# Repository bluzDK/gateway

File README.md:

Bluz Gateway Hardware Files
==========
Bluz is a Development Kit (DK) that implements the Wiring language and talks to the [Particle](https://www.particle.io/) cloud through Bluetooth Low Energy. It can be accessed through a REST API and programmed from a Web IDE.

These files have been made available online through a [Creative Commons Attribution-ShareAlike 3.0](http://creativecommons.org/licenses/by-sa/3.0/) license.

You are welcome to distribute, remix, and use these files for commercial purposes. If you do so, please attribute the original design to Bluz both on the website and on the physical packaging of the product or in the instruction manual. All derivative works must be published under the same or a similar license.

All items are subject to change over time as the product is designed, so make sure you are always looking at the latest information by pulling often.

##Sections
<b>BOM</b>: Current Bill of Materials for the gateway.

<b>Datasheets</b>: Datasheets for all major parts on the board.

<b>HW Design</b>: Schematics, board layouts, and other design files.

<b>3D Files</b>: 3D Models of the PCBA and Case

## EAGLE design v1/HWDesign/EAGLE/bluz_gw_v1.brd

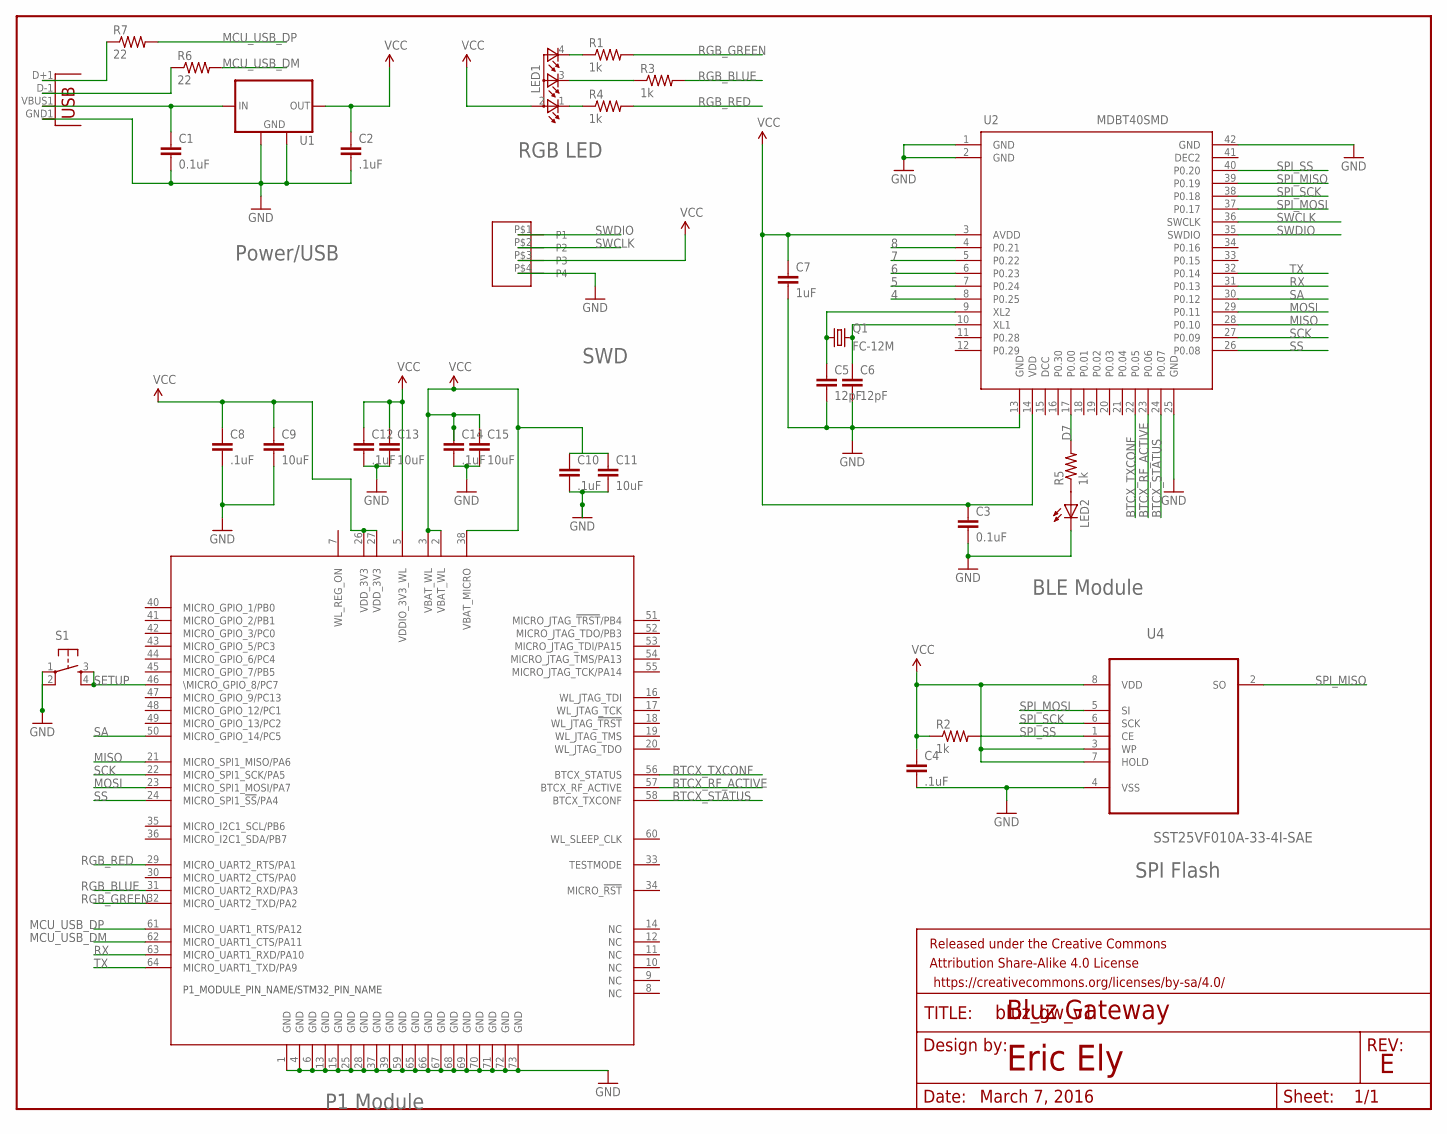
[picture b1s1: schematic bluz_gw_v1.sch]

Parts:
C1, C3: 0.1uF; 0603-CAP
C2, C4, C8, C10, C12, C14: .1uF; 0603-CAP
C5, C6: 12pF; 0603-CAP
C7: 1uF; 0603-CAP
C9, C11, C13, C15: 10uF; 0603-CAP
FRAME1: FRAME-LETTER; CREATIVE_COMMONS
JP2: USBA-SMD-MALE; USB-A-SMT-MALE
LED1: TOPLED-3PLCC; P-LCC-4-3
LED2: LEDCHIP-LED0603; CHIP-LED0603
Q1: FC-12M
R1, R2, R3, R4, R5: 1k; 0603-RES
R6, R7: 22; 0603-RES
S1: TAC_SWITCHSMD; TACTILE_SWITCH_SMD
U1: MCP1825S-SOT223; SOT223
U2: MDBT40SMD; MDBT40
U3: WM-N-BM-14
U4: SST25VF010A-33-4I-SAE; SOIC127P600X175-8N
U$3: POGO_CONNECTORPOGO_CONNECTOR; POGO_CONNECTER

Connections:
4: U2.8 (P0.25)
5: U2.7 (P0.24)
6: U2.6 (P0.23)
7: U2.5 (P0.22)
8: U2.4 (P0.21)
BTCX_RF_ACTIVE: U2.23 (P0.06), U3.57 (BTCX_RF_ACTIVE)
BTCX_STATUS: U2.24 (P0.07), U3.58 (BTCX_TXCONF)
BTCX_TXCONF: U2.22 (P0.05), U3.56 (BTCX_STATUS)
D7: R5.2, U2.17 (P0.00)
GND: C1.2, C2.2, C3.2, C4.2, C5.2, C6.2, C7.2, C8.2, C9.2, C10.2, C11.2, C12.2, C13.2, C14.2, C15.2, JP2.GND1 (GND), LED2.C, S1.1, S1.2, U1.2 (GND), U1.4 (GND), U2.1 (GND), U2.2 (GND), U2.13 (GND), U2.25 (GND), U2.42 (GND), U3.1 (GND), U3.4 (GND), U3.6 (GND), U3.13 (GND), U3.15 (GND), U3.25 (GND), U3.28 (GND), U3.37 (GND), U3.39 (GND), U3.59 (GND), U3.65 (GND), U3.66 (GND), U3.67 (GND), U3.68 (GND), U3.69 (GND), U3.70 (GND), U3.71 (GND), U3.72 (GND), U3.73 (GND), U4.4 (VSS), U$3.P$4 (P4)
MCU_USB_DM: R6.2, U3.62 (MICRO_UART1_CTS/PA11)
MCU_USB_DP: R7.2, U3.61 (MICRO_UART1_RTS/PA12)
MISO: U2.28 (P0.10), U3.21 (MICRO_SPI1_MISO/PA6)
MOSI: U2.29 (P0.11), U3.23 (MICRO_SPI1_MOSI/PA7)
unnamed: C1.1, JP2.VBUS1 (VBUS), U1.1 (IN)
unnamed: LED1.4 (CGREEN), R1.1
unnamed: LED1.3 (CBLUE), R3.1
unnamed: LED1.1 (CRED), R4.1
unnamed: JP2.D-1 (D-), R6.1
unnamed: JP2.D+1 (D+), R7.1
unnamed: C5.1, Q1.1, U2.9 (XL2)
unnamed: C6.1, Q1.2, U2.10 (XL1)
unnamed: LED2.A, R5.1
RGB_BLUE: R3.2, U3.31 (MICRO_UART2_RXD/PA3)
RGB_GREEN: R1.2, U3.32 (MICRO_UART2_TXD/PA2)
RGB_RED: R4.2, U3.29 (MICRO_UART2_RTS/PA1)
RX: U2.31 (P0.13), U3.63 (MICRO_UART1_RXD/PA10)
SA: U2.30 (P0.12), U3.50 (MICRO_GPIO_14/PC5)
SCK: U2.27 (P0.09), U3.22 (MICRO_SPI1_SCK/PA5)
SETUP: S1.3, S1.4, U3.46 (\MICRO_GPIO_8/PC7)
SPI_MISO: U2.39 (P0.19), U4.2 (SO)
SPI_MOSI: U2.37 (P0.17), U4.5 (SI)
SPI_SCK: U2.38 (P0.18), U4.6 (SCK)
SPI_SS: R2.2, U2.40 (P0.20), U4.1 (CE)
SS: U2.26 (P0.08), U3.24 (MICRO_SPI1_!SS!/PA4)
SWCLK: U2.36 (SWCLK), U$3.P$2 (P2)
SWDIO: U2.35 (SWDIO), U$3.P$1 (P1)
TX: U2.32 (P0.14), U3.64 (MICRO_UART1_TXD/PA9)
VCC: C2.1, C3.1, C4.1, C7.1, C8.1, C9.1, C10.1, C11.1, C12.1, C13.1, C14.1, C15.1, LED1.2 (A2), R2.1, U1.3 (OUT), U2.3 (AVDD), U2.14 (VDD), U3.2 (VBAT_WL), U3.3 (VBAT_WL), U3.5 (VDDIO_3V3_WL), U3.26 (VDD_3V3), U3.27 (VDD_3V3), U3.38 (VBAT_MICRO), U4.3 (WP), U4.7 (HOLD), U4.8 (VDD), U$3.P$3 (P3)

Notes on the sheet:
P1 Module
Power/USB
BLE Module
SWD
Eric Ely
Bluz Gateway
March 7, 2016
SPI Flash
RGB LED

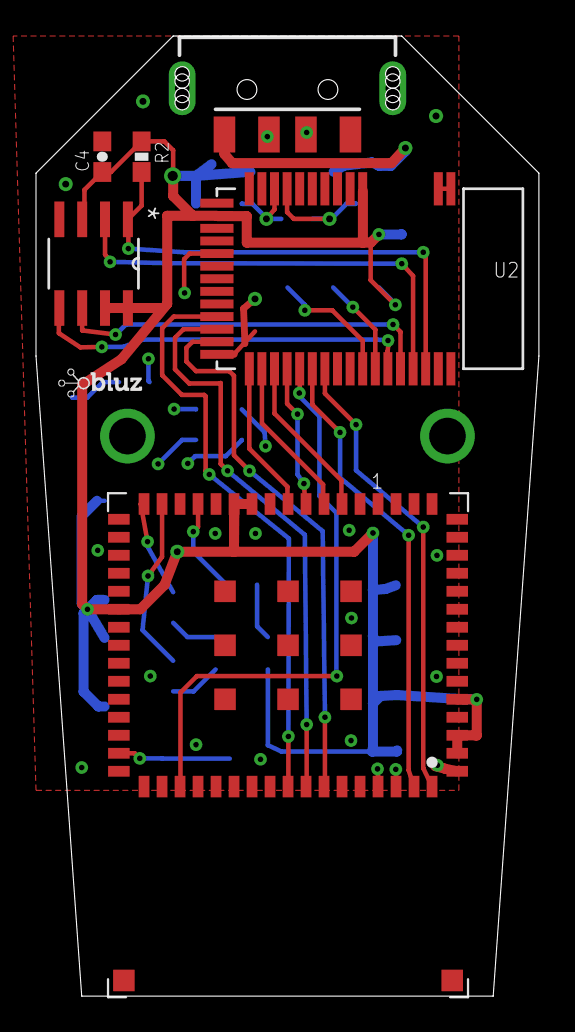
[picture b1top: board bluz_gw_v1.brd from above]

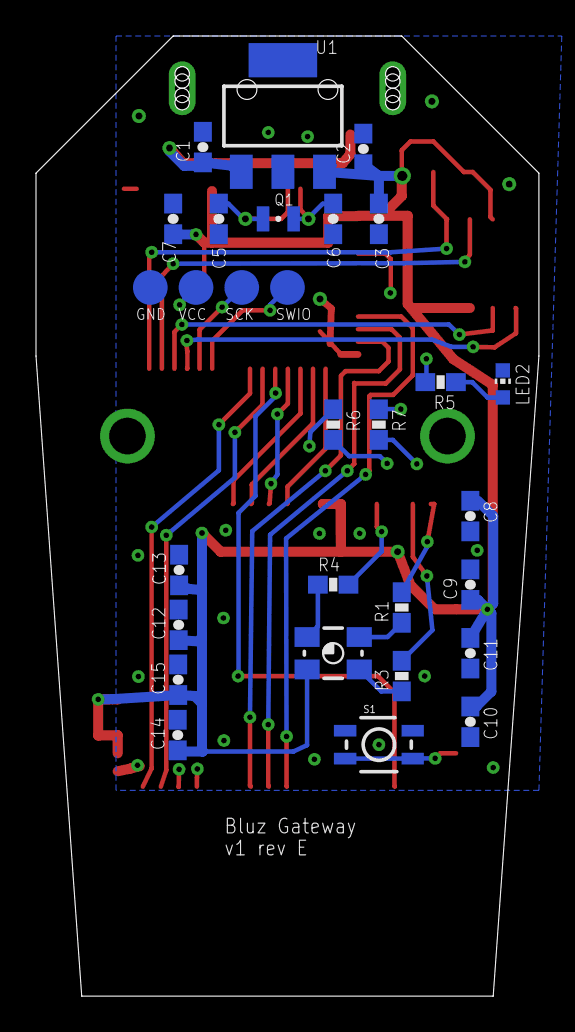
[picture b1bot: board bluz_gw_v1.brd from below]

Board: 2 copper layers, 27.9 x 53.3 mm, 34 parts (26 on the bottom side), 34 nets.

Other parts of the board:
U$2: BLUZE_LOGO_LOW_RES

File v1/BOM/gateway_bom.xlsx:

Part(s) | Package | Value | Description | Qty | Manufacturer | Mfg. Part Number | Data Sheet | Notes
U2 | SMD |  | nrf51822 module with 32K RAM | 1 | Raytac | MDBT40 | data
U1 | SOT-23 |  | Linear Regulator with 3.3V output | 1 | Microchip | MCP1825S-3302E/DB | data
U3 | SMD |  | Particle P1 Module | 1 | Particle | P1 | data
U4 | SOIC-8 |  | 2Mb SPI Flash | 1 | Microchip | SST25VF020-20-4I-SAE | data
Q1 |  | 32.768KHz | 20ppm, 9pF, 32.768KHz crystal | 1 |  | ABS06-32.768KHZ-9-T | data
C1-C4, C8, C10, C12, C14 | 0603 | 0.1uF | 0603 Package | 8 |  | GRM188R71C104KA01D | data
C5, C6 | 0603 | 12pF | 0603 Package | 2 |  | CL10C120JB8NNNC | data
C7 | 0603 | 1uF | 0603 Package | 1 |  | CL10B105KP8NNNC | data
C9, C11, C13, C15 | 0603 | 10uF | 0603 Package | 4 |  | CL10A106MQ8NNNC | data
R1-R4 | 0603 | 1K Ohm | 1k Ohm | 4 |  | CRCW06031K00FKEA | data
L1 | SMD |  | 3.2mm x 2.7m RGB LED | 1 |  | 597-7701-207F | data
J1 | Thru |  | USB A Male Connector | 1 | Molex | 480371000 | data

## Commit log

2015-11-17 new design files
2017-03-21 updated hw design files
2017-03-28 correct BOM

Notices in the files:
parts and their libraries:
SparkFun-Passives: Licensing: Creative Commons ShareAlike 4.0 International - https://creativecommons.org/licenses/by-sa/4.0
SparkFun-Aesthetics: Released under the Creative Commons Attribution Share-Alike 4.0 License
SparkFun-Aesthetics: https://creativecommons.org/licenses/by-sa/4.0
